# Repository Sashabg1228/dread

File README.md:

# dread
Version 1 of the battlebot was sawbot battlebot inspired by Sawblaze
It was made for the event TuesBattlebots 2023.
The project was developed from December 2022 to June 2023.

Version 2 of the robot is used for graduation project in school.
The type of the robot is changed from sawbot to hammersaw, meaning the saw no longer has the function of cutting but of striking the opponents. The work on this version started at the end of September 2023.

Link to github repo:
https://github.com/Sashabg1228/dread.git

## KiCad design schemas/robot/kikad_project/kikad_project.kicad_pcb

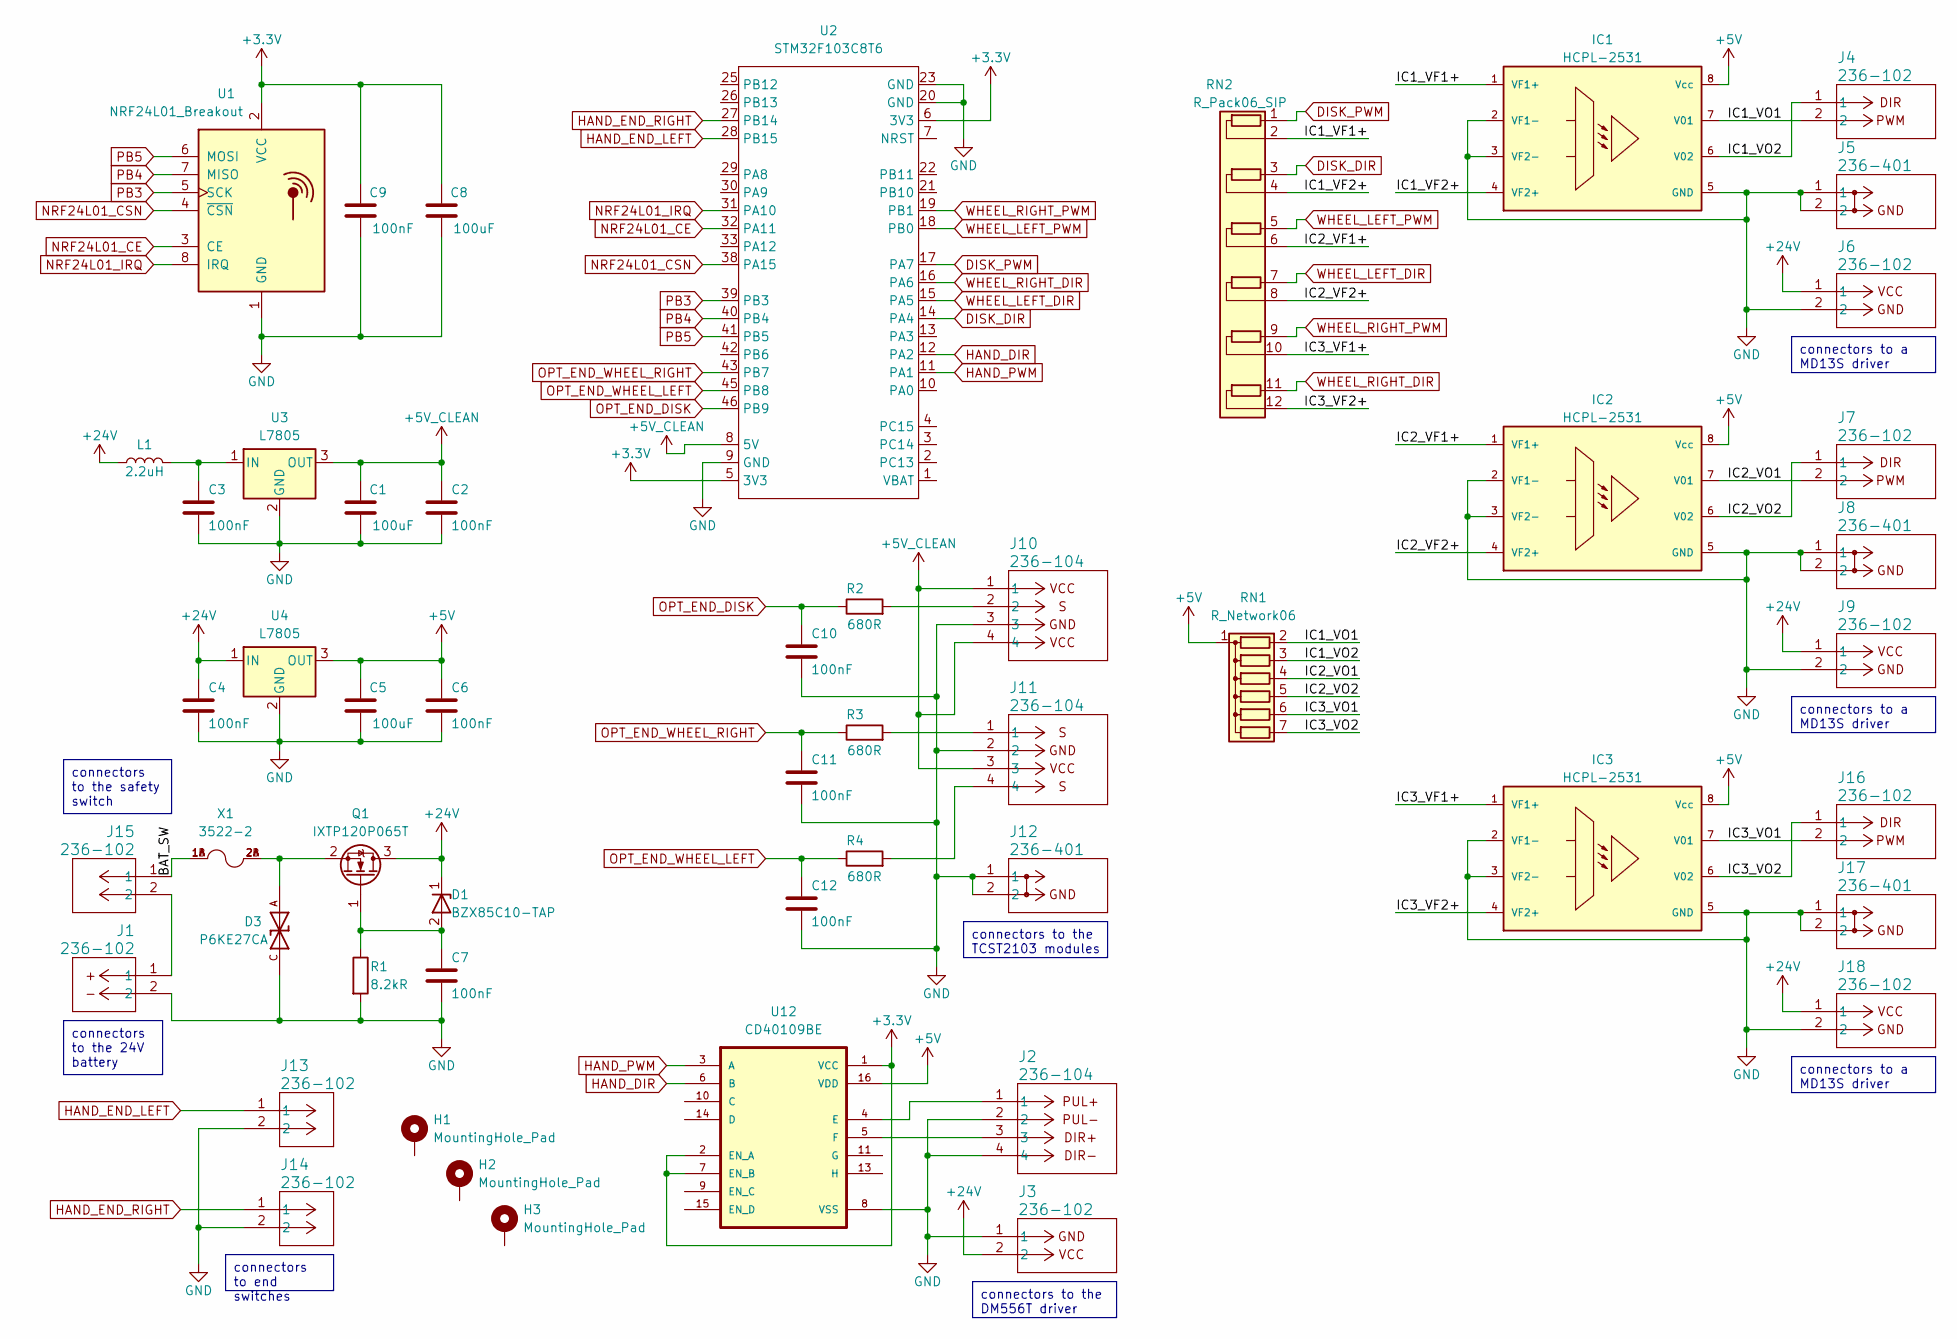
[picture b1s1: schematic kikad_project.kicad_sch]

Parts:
C1, C5, C8: 100uF; CP_Radial_D5.0mm_P2.00mm
C2, C3, C4, C6, C7, C9, C10, C11, C12: 100nF; C_Rect_L4.6mm_W3.8mm_P2.50mm_MKS02_FKP02
D1: BZX85C10-TAP; DO-41_VIS
D3: P6KE27CA; DIOAD1300W80L670D310; PARTREV K2105
H1, H2, H3: MountingHole_Pad; MountingHole_3.2mm_M3_Pad
IC1, IC2, IC3: HCPL-2531; DIL08; MPN HCPL-2531A-000E
J1, J3, J4, J6, J7, J9, J13, J14, J15, J16, J18: 236-102; CONN_236-102_WAG
J2, J10, J11: 236-104; CONN_236-104_WAG
J5, J8, J12, J17: 236-401; 236-744_WAG
L1: 2.2uH; L_Axial_L16.0mm_D7.5mm_P5.08mm_Vertical_Fastron_XHBCC
Q1: IXTP120P065T; TO-220-3_Vertical
R1: 8.2kR; R_Axial_DIN0207_L6.3mm_D2.5mm_P10.16mm_Horizontal
R2, R3, R4: 680R; R_Axial_DIN0207_L6.3mm_D2.5mm_P10.16mm_Horizontal
RN1: R_Network06; R_Array_SIP7
RN2: R_Pack06_SIP; R_Array_SIP12
U1: NRF24L01_Breakout; nRF24L01_Breakout
U2: STM32F103C8T6; STM32F103C8T6_pinout
U3, U4: L7805; TO-220-3_Vertical
U12: CD40109BE; DIP794W45P254L1969H508Q16; DigiKey_Part_Number 2156-CD40109BE-ND
X1: 3522-2; FUSE_3522-2; PARTREV J

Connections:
+3.3V: C8.1, C9.1, U1.2 (VCC), U2.5 (3V3), U2.6 (3V3), U12.1 (VCC), U12.2 (EN_A), U12.7 (EN_B)
+5V: C5.1, C6.1, IC1.8 (Vcc), IC2.8 (Vcc), IC3.8 (Vcc), RN1.1 (common), U4.3 (OUT), U12.16 (VDD)
+24V: C4.1, D1.1, J3.2, J6.1, J9.1, J18.1, L1.1, Q1.3 (D), U4.1 (IN)
/BAT_SW: J15.1, X1.1A, X1.1B
/IC1_VF1+: IC1.1 (VF1+), RN2.2 (R1.2)
/IC1_VF2+: IC1.4 (VF2+), RN2.4 (R2.2)
/IC1_VO1: IC1.7 (V01), J4.2, RN1.2 (R1)
/IC1_VO2: IC1.6 (V02), J4.1, RN1.3 (R2)
/IC2_VF1+: IC2.1 (VF1+), RN2.6 (R3.2)
/IC2_VF2+: IC2.4 (VF2+), RN2.8 (R4.2)
/IC2_VO1: IC2.7 (V01), J7.2, RN1.4 (R3)
/IC2_VO2: IC2.6 (V02), J7.1, RN1.5 (R4)
/IC3_VF1+: IC3.1 (VF1+), RN2.10 (R5.2)
/IC3_VF2+: IC3.4 (VF2+), RN2.12 (R6.2)
/IC3_VO1: IC3.7 (V01), J16.2, RN1.6 (R5)
/IC3_VO2: IC3.6 (V02), J16.1, RN1.7 (R6)
DISK_DIR: RN2.3 (R2.1), U2.14 (PA4)
DISK_PWM: RN2.1 (R1.1), U2.17 (PA7)
GND: C1.2, C2.2, C3.2, C4.2, C5.2, C6.2, C7.2, C8.2, C9.2, C10.2, C11.2, C12.2, D3.C, IC1.2 (VF1-), IC1.3 (VF2-), IC1.5 (GND), IC2.2 (VF1-), IC2.3 (VF2-), IC2.5 (GND), IC3.2 (VF1-), IC3.3 (VF2-), IC3.5 (GND), J1.2, J2.2, J2.4, J3.1, J5.1, J5.2, J6.2, J8.1, J8.2, J9.2, J10.3, J11.2, J12.1, J12.2, J13.2, J14.2, J17.1, J17.2, J18.2, R1.2, U1.1 (GND), U2.9 (GND), U2.20 (GND), U2.23 (GND), U3.2 (GND), U4.2 (GND), U12.8 (VSS)
HAND_DIR: U2.12 (PA2), U12.6 (B)
HAND_END_LEFT: J13.1, U2.28 (PB15)
HAND_END_RIGHT: J14.1, U2.27 (PB14)
HAND_PWM: U2.11 (PA1), U12.3 (A)
NRF24L01_CE: U1.3 (CE), U2.32 (PA11)
NRF24L01_CSN: U1.4 (~CSN), U2.38 (PA15)
NRF24L01_IRQ: U1.8 (IRQ), U2.31 (PA10)
unnamed: J1.1, J15.2
unnamed: J10.2, R2.2
unnamed: J11.1, R3.2
unnamed: J11.4, R4.2
unnamed: C7.1, D1.2, Q1.1 (G), R1.1
unnamed: D3.A, Q1.2 (S), X1.2A, X1.2B
unnamed: C3.1, L1.2, U3.1 (IN)
unnamed: J2.1, U12.4 (E)
unnamed: J2.3, U12.5 (F)
OPT_END_DISK: C10.1, R2.1, U2.46 (PB9)
OPT_END_WHEEL_LEFT: C12.1, R4.1, U2.45 (PB8)
OPT_END_WHEEL_RIGHT: C11.1, R3.1, U2.43 (PB7)
PB3: U1.5 (SCK), U2.39 (PB3)
PB4: U1.7 (MISO), U2.40 (PB4)
PB5: U1.6 (MOSI), U2.41 (PB5)
VCC: C1.1, C2.1, J10.1, J10.4, J11.3, U2.8 (5V), U3.3 (OUT)
WHEEL_LEFT_DIR: RN2.7 (R4.1), U2.15 (PA5)
WHEEL_LEFT_PWM: RN2.5 (R3.1), U2.18 (PB0)
WHEEL_RIGHT_DIR: RN2.11 (R6.1), U2.16 (PA6)
WHEEL_RIGHT_PWM: RN2.9 (R5.1), U2.19 (PB1)

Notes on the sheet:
connectors to the 24V battery
connectors to end switches
connectors to a MD13S driver
connectors to the DM556T driver
connectors to the safety switch
connectors to the TCST2103 modules

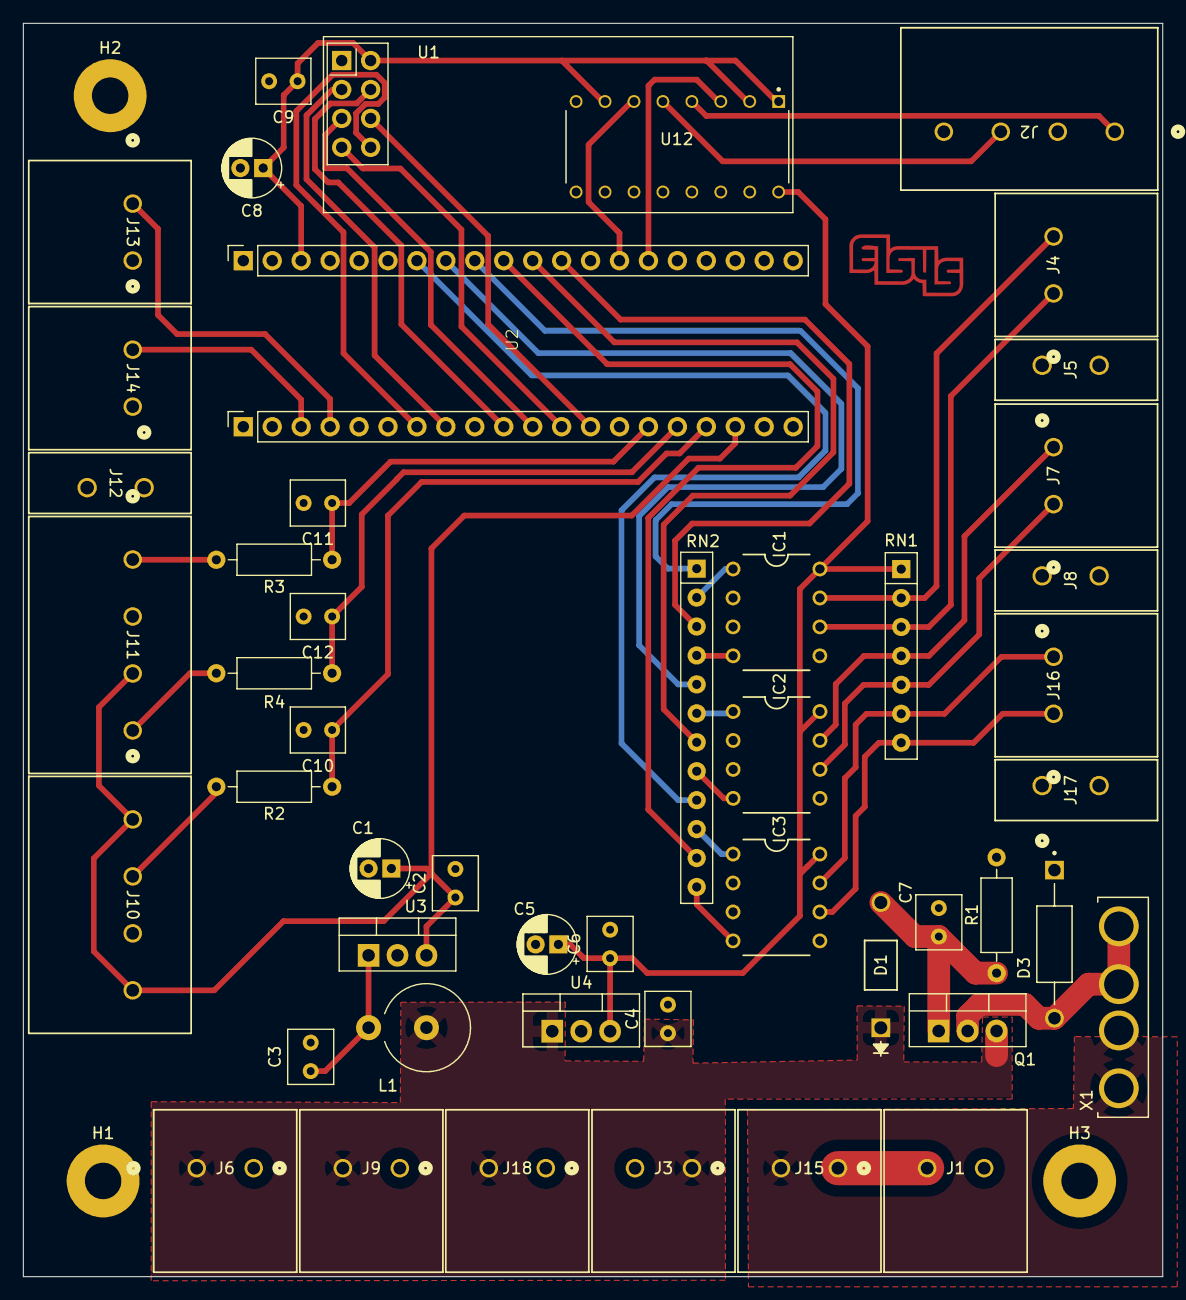
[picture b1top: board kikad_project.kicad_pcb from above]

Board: 2 copper layers, 100.0 x 110.0 mm, 52 parts (0 on the bottom side), 46 nets.

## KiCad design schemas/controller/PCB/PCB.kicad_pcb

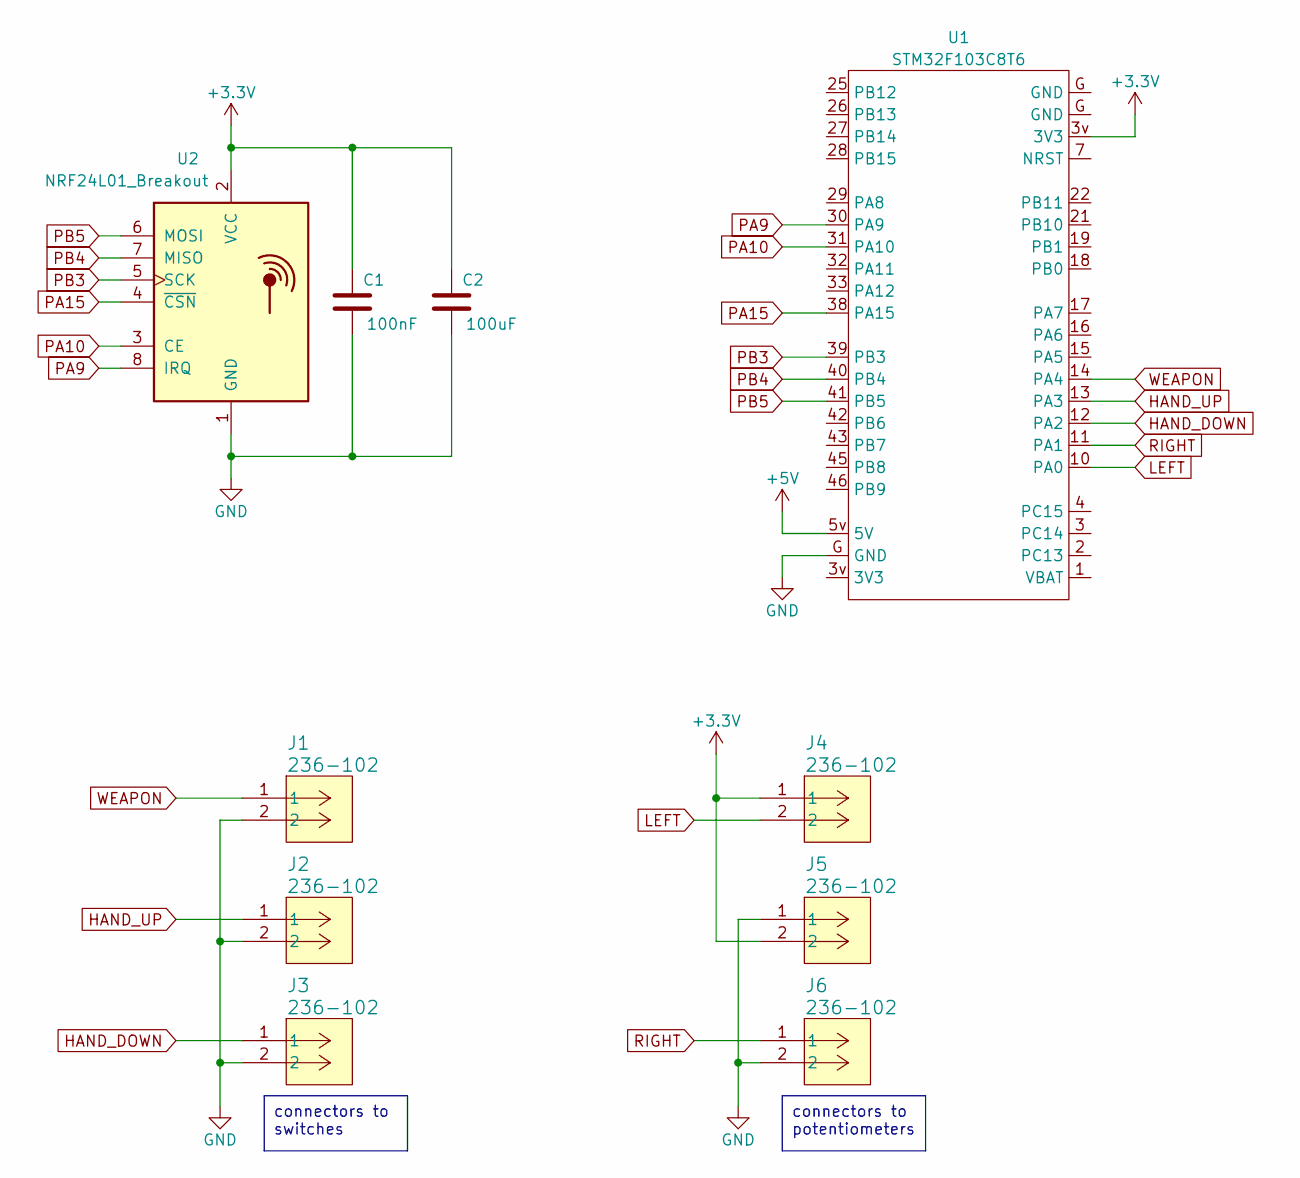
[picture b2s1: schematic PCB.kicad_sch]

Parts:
C1: 100nF; C_Axial_L5.1mm_D3.1mm_P7.50mm_Horizontal
C2: 100uF; CP_Radial_D5.0mm_P2.00mm
J1, J2, J3, J4, J5, J6: 236-102; CONN_236-102_WAG
U1: STM32F103C8T6; STM32F103C8T6_pinout
U2: NRF24L01_Breakout; nRF24L01_Breakout

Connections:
+3.3V: C1.1, C2.1, J4.1, J5.2, U1.3v (3V3), U2.2 (VCC)
+5V: U1.5v (5V)
GND: C1.2, C2.2, J1.2, J2.2, J3.2, J5.1, J6.2, U1.G (GND), U2.1 (GND)
HAND_DOWN: J3.1, U1.12 (PA2)
HAND_UP: J2.1, U1.13 (PA3)
LEFT: J4.2, U1.10 (PA0)
PA9: U1.30 (PA9), U2.8 (IRQ)
PA10: U1.31 (PA10), U2.3 (CE)
PA15: U1.38 (PA15), U2.4 (~CSN)
PB3: U1.39 (PB3), U2.5 (SCK)
PB4: U1.40 (PB4), U2.7 (MISO)
PB5: U1.41 (PB5), U2.6 (MOSI)
RIGHT: J6.1, U1.11 (PA1)
WEAPON: J1.1, U1.14 (PA4)

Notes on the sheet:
connectors to switches
connectors to potentiometers

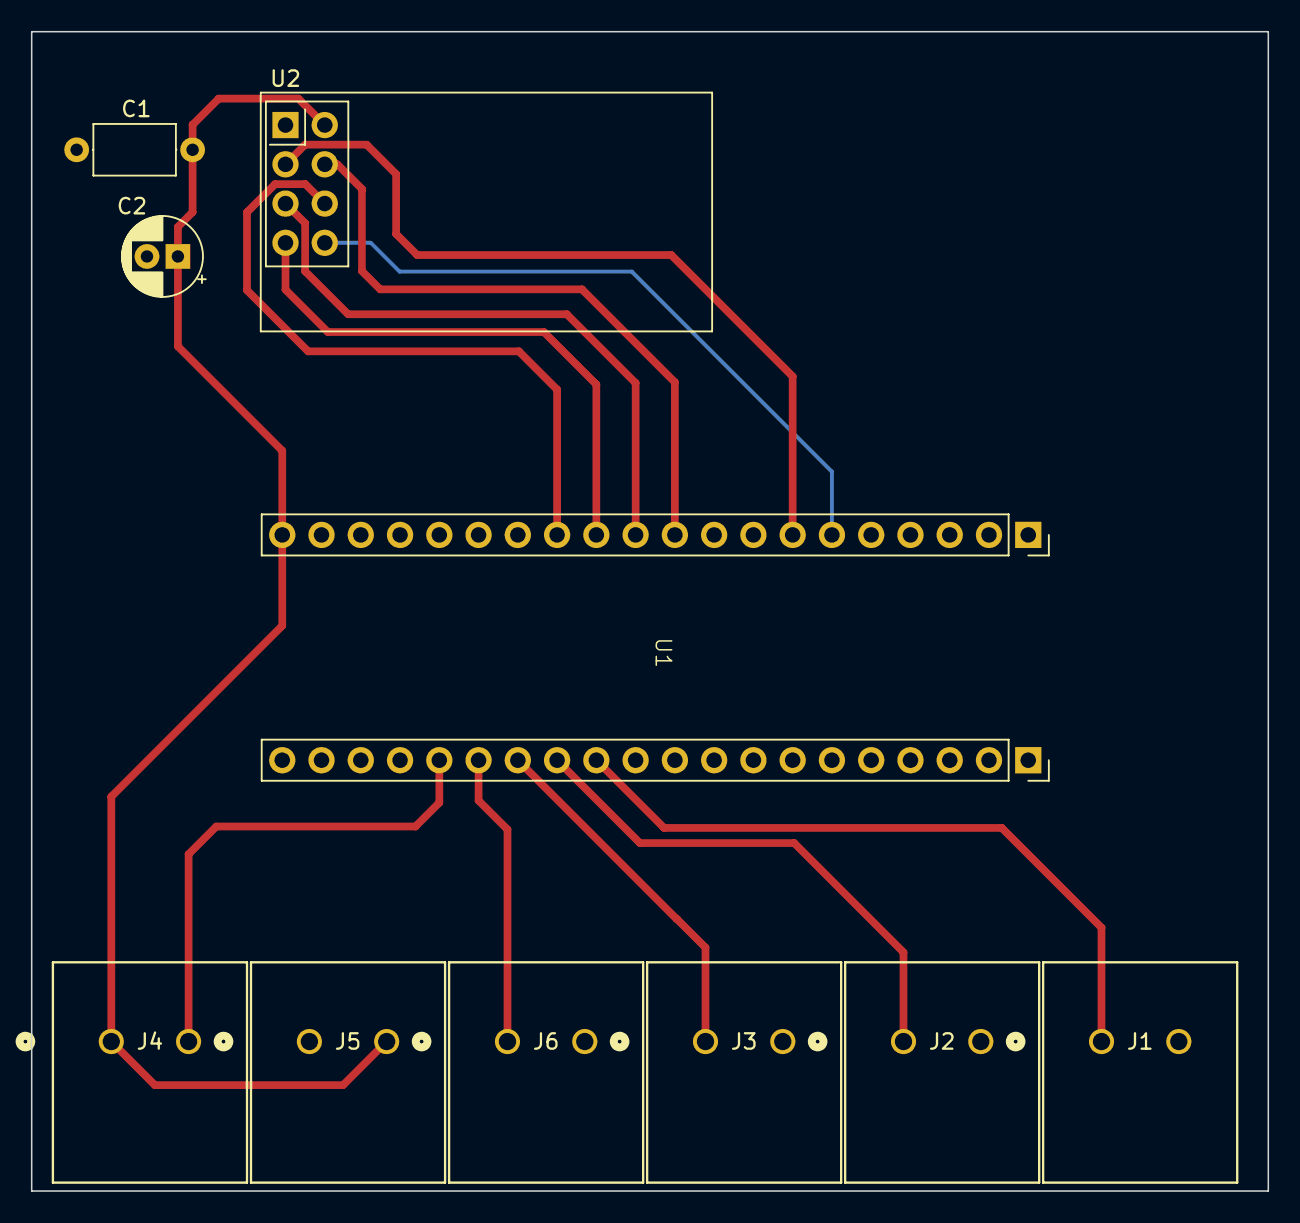
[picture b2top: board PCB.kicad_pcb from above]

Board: 2 copper layers, 80.0 x 75.0 mm, 10 parts (0 on the bottom side), 13 nets.

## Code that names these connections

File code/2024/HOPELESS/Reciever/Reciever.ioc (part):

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Mcu.Name=STM32F103C(8-B)Tx
Mcu.Package=LQFP48
Mcu.UserName=STM32F103C8Tx
PA1.GPIOParameters=GPIO_Label
PA1.GPIO_Label=HAND_PWM
PA1.Signal=GPIO_Output
PA10.GPIOParameters=GPIO_Label
PA10.GPIO_Label=NRF24L01_IRQ
PA10.Signal=GPXTI10
PA11.GPIOParameters=GPIO_Label
PA11.GPIO_Label=NRF24L01_CE
PA11.Signal=GPIO_Output
PA13.Mode=Serial_Wire
PA13.Signal=SYS_JTMS-SWDIO
PA14.Mode=Serial_Wire
PA14.Signal=SYS_JTCK-SWCLK
PA15.GPIOParameters=GPIO_Label
PA15.GPIO_Label=NRF24L01_CSN
PA15.Signal=GPIO_Output
PA2.GPIOParameters=GPIO_Label
PA2.GPIO_Label=HAND_DIR
PA2.Signal=GPIO_Output
PA4.GPIOParameters=GPIO_Label
PA4.GPIO_Label=DISK_DIR
PA4.Signal=GPIO_Output
PA5.GPIOParameters=GPIO_Label
PA5.GPIO_Label=WHEEL_LEFT_DIR
PA5.Signal=GPIO_Output
PA6.GPIOParameters=GPIO_Label
PA6.GPIO_Label=WHEEL_RIGHT_DIR
PA6.Signal=GPIO_Output
PA7.GPIOParameters=GPIO_Label
PA7.GPIO_Label=DISK_PWM
PA7.Signal=S_TIM3_CH2
PB0.GPIOParameters=GPIO_Label
PB0.GPIO_Label=WHEEL_LEFT_PWM
PB0.Signal=S_TIM3_CH3
PB1.GPIOParameters=GPIO_Label
PB1.GPIO_Label=WHEEL_RIGHT_PWM
PB1.Signal=S_TIM3_CH4
PB14.GPIOParameters=GPIO_PuPd,GPIO_Label,GPIO_ModeDefaultEXTI
PB14.GPIO_Label=HAND_END_RIGHT
PB14.GPIO_ModeDefaultEXTI=GPIO_MODE_IT_RISING_FALLING
PB14.GPIO_PuPd=GPIO_PULLUP
PB14.Signal=GPXTI14
PB15.GPIOParameters=GPIO_PuPd,GPIO_Label,GPIO_ModeDefaultEXTI
PB15.GPIO_Label=HAND_END_LEFT
PB15.GPIO_ModeDefaultEXTI=GPIO_MODE_IT_RISING_FALLING
PB15.GPIO_PuPd=GPIO_PULLUP
PB15.Signal=GPXTI15
PB3.Mode=Full_Duplex_Master
PB3.Signal=SPI1_SCK
PB4.Mode=Full_Duplex_Master
PB4.Signal=SPI1_MISO
PB5.Mode=Full_Duplex_Master
PB5.Signal=SPI1_MOSI
PB7.GPIOParameters=GPIO_PuPd,GPIO_Label,GPIO_ModeDefaultEXTI
PB7.GPIO_Label=OPT_END_WHEEL_RIGHT
PB7.GPIO_ModeDefaultEXTI=GPIO_MODE_IT_FALLING
PB7.GPIO_PuPd=GPIO_PULLUP
PB7.Signal=GPXTI7
PB8.GPIOParameters=GPIO_PuPd,GPIO_Label,GPIO_ModeDefaultEXTI
PB8.GPIO_Label=OPT_END_WHEEL_LEFT
PB8.GPIO_ModeDefaultEXTI=GPIO_MODE_IT_FALLING
PB8.GPIO_PuPd=GPIO_PULLUP
PB8.Signal=GPXTI8
PB9.GPIOParameters=GPIO_PuPd,GPIO_Label,GPIO_ModeDefaultEXTI
PB9.GPIO_Label=OPT_END_DISK
PB9.GPIO_ModeDefaultEXTI=GPIO_MODE_IT_FALLING
PB9.GPIO_PuPd=GPIO_PULLUP
PB9.Signal=GPXTI9
PC13-TAMPER-RTC.Signal=GPIO_Output
PC14-OSC32_IN.Mode=LSE-External-Oscillator
PC14-OSC32_IN.Signal=RCC_OSC32_IN
PC15-OSC32_OUT.Mode=LSE-External-Oscillator
PC15-OSC32_OUT.Signal=RCC_OSC32_OUT
PD0-OSC_IN.Mode=HSE-External-Oscillator
PD0-OSC_IN.Signal=RCC_OSC_IN
PD1-OSC_OUT.Mode=HSE-External-Oscillator
PD1-OSC_OUT.Signal=RCC_OSC_OUT
RCC.SYSCLKFreq_VALUE=72000000
RCC.SYSCLKSource=RCC_SYSCLKSOURCE_PLLCLK
board=custom

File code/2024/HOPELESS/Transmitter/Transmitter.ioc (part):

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Mcu.Name=STM32F103C(8-B)Tx
Mcu.Package=LQFP48
Mcu.UserName=STM32F103C8Tx
PA0-WKUP.GPIOParameters=GPIO_Label
PA0-WKUP.GPIO_Label=LEFT
PA0-WKUP.Signal=SharedAnalog_PA0
PA1.GPIOParameters=GPIO_Label
PA1.GPIO_Label=RIGHT
PA1.Signal=SharedAnalog_PA1
PA10.GPIOParameters=GPIO_Label
PA10.GPIO_Label=NRF24L01_CE
PA10.Signal=GPIO_Output
PA13.Mode=Serial_Wire
PA13.Signal=SYS_JTMS-SWDIO
PA14.Mode=Serial_Wire
PA14.Signal=SYS_JTCK-SWCLK
PA15.GPIOParameters=GPIO_Label
PA15.GPIO_Label=NRF24L01_CSN
PA15.Signal=GPIO_Output
PA2.GPIOParameters=GPIO_PuPd,GPIO_Label,GPIO_ModeDefaultEXTI
PA2.GPIO_Label=HAND_DOWN
PA2.GPIO_ModeDefaultEXTI=GPIO_MODE_IT_RISING_FALLING
PA2.GPIO_PuPd=GPIO_PULLUP
PA2.Signal=GPXTI2
PA3.GPIOParameters=GPIO_PuPd,GPIO_Label,GPIO_ModeDefaultEXTI
PA3.GPIO_Label=HAND_UP
PA3.GPIO_ModeDefaultEXTI=GPIO_MODE_IT_RISING_FALLING
PA3.GPIO_PuPd=GPIO_PULLUP
PA3.Signal=GPXTI3
PA4.GPIOParameters=GPIO_PuPd,GPIO_Label,GPIO_ModeDefaultEXTI
PA4.GPIO_Label=WEAPON
PA4.GPIO_ModeDefaultEXTI=GPIO_MODE_IT_FALLING
PA4.GPIO_PuPd=GPIO_PULLUP
PA4.Signal=GPXTI4
PA9.GPIOParameters=GPIO_Label
PA9.GPIO_Label=NRF24L01_IRQ
PA9.Signal=GPIO_Input
PB3.Mode=Full_Duplex_Master
PB3.Signal=SPI1_SCK
PB4.Mode=Full_Duplex_Master
PB4.Signal=SPI1_MISO
PB5.Mode=Full_Duplex_Master
PB5.Signal=SPI1_MOSI
PC13-TAMPER-RTC.Signal=GPIO_Output
PC14-OSC32_IN.Mode=LSE-External-Oscillator
PC14-OSC32_IN.Signal=RCC_OSC32_IN
PC15-OSC32_OUT.Mode=LSE-External-Oscillator
PC15-OSC32_OUT.Signal=RCC_OSC32_OUT
PD0-OSC_IN.Mode=HSE-External-Oscillator
PD0-OSC_IN.Signal=RCC_OSC_IN
PD1-OSC_OUT.Mode=HSE-External-Oscillator
PD1-OSC_OUT.Signal=RCC_OSC_OUT
RCC.SYSCLKFreq_VALUE=72000000
RCC.SYSCLKSource=RCC_SYSCLKSOURCE_PLLCLK
board=custom

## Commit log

2023-06-11 project upload
2023-12-17 Start of work on ver2. Upload of the current progress
    Work on version 2 has started. What is done until now:
    * 3d model of the robot
    + the needed files for laser cutting
    * started making the electric scheme of the robot (still not ready)
    * started making the electric scheme of the joysticks (still not ready)
2023-12-17 3d model of the robot upload
2023-12-19 Schematics ready(excluding PCB design)
    The electric schema for the PCB in the robot and the mounting schema are ready. The footprints for each element are present. However, the PCB design is not ready.
2023-12-22 control upload
2023-12-24 PCB ready
2024-01-02 minor changes to PCB layout + major changes to mounting schema
2024-01-02 controler PCB version 1
2024-01-03 upload of components' datasheets
2024-01-05 small edits to robot PCB schema and pcb layout
2024-01-17 small changes to the PCB layout
2024-02-18 regular upload
    1. mid production documentation
    2. minor edits on the electrical schemas
    3. small changes to the 3d model of the robot
    4. first try to wrtie the necessary code
2024-02-19 help
2024-02-19 praying
2024-02-20 thank god TX works
2024-02-21 praise god both the receiver and transmitter work
2024-02-21 soft link experiment
2024-02-22 library update
    + payload typedef
    + dynamic allocation of the buffers
2024-02-25 Almost ready transmitter and second version of receiver
    The lord and saviour bestowed upon me the power to complete the transmitter and the second version of the receiver
    NB: the clock of the transmitter must be edited
2024-02-25 Almost ready transmitter and almost ready receiver
2024-02-25 Almost ready transmitter and almost ready receiver
    NB: there is a mess with the interrupts
2024-02-27 PCB edit + other minor changes
2024-02-28 hopeless situation
    * documentation update
    * code update
2024-02-29 Documentation ready
    Bless the holly lord and saviour!!!
2024-03-01 submit
    edited documentation ready
    3d model link made
2024-03-16 upload
2024-04-27 changes on the project structure
2024-04-29 robot schema edit
